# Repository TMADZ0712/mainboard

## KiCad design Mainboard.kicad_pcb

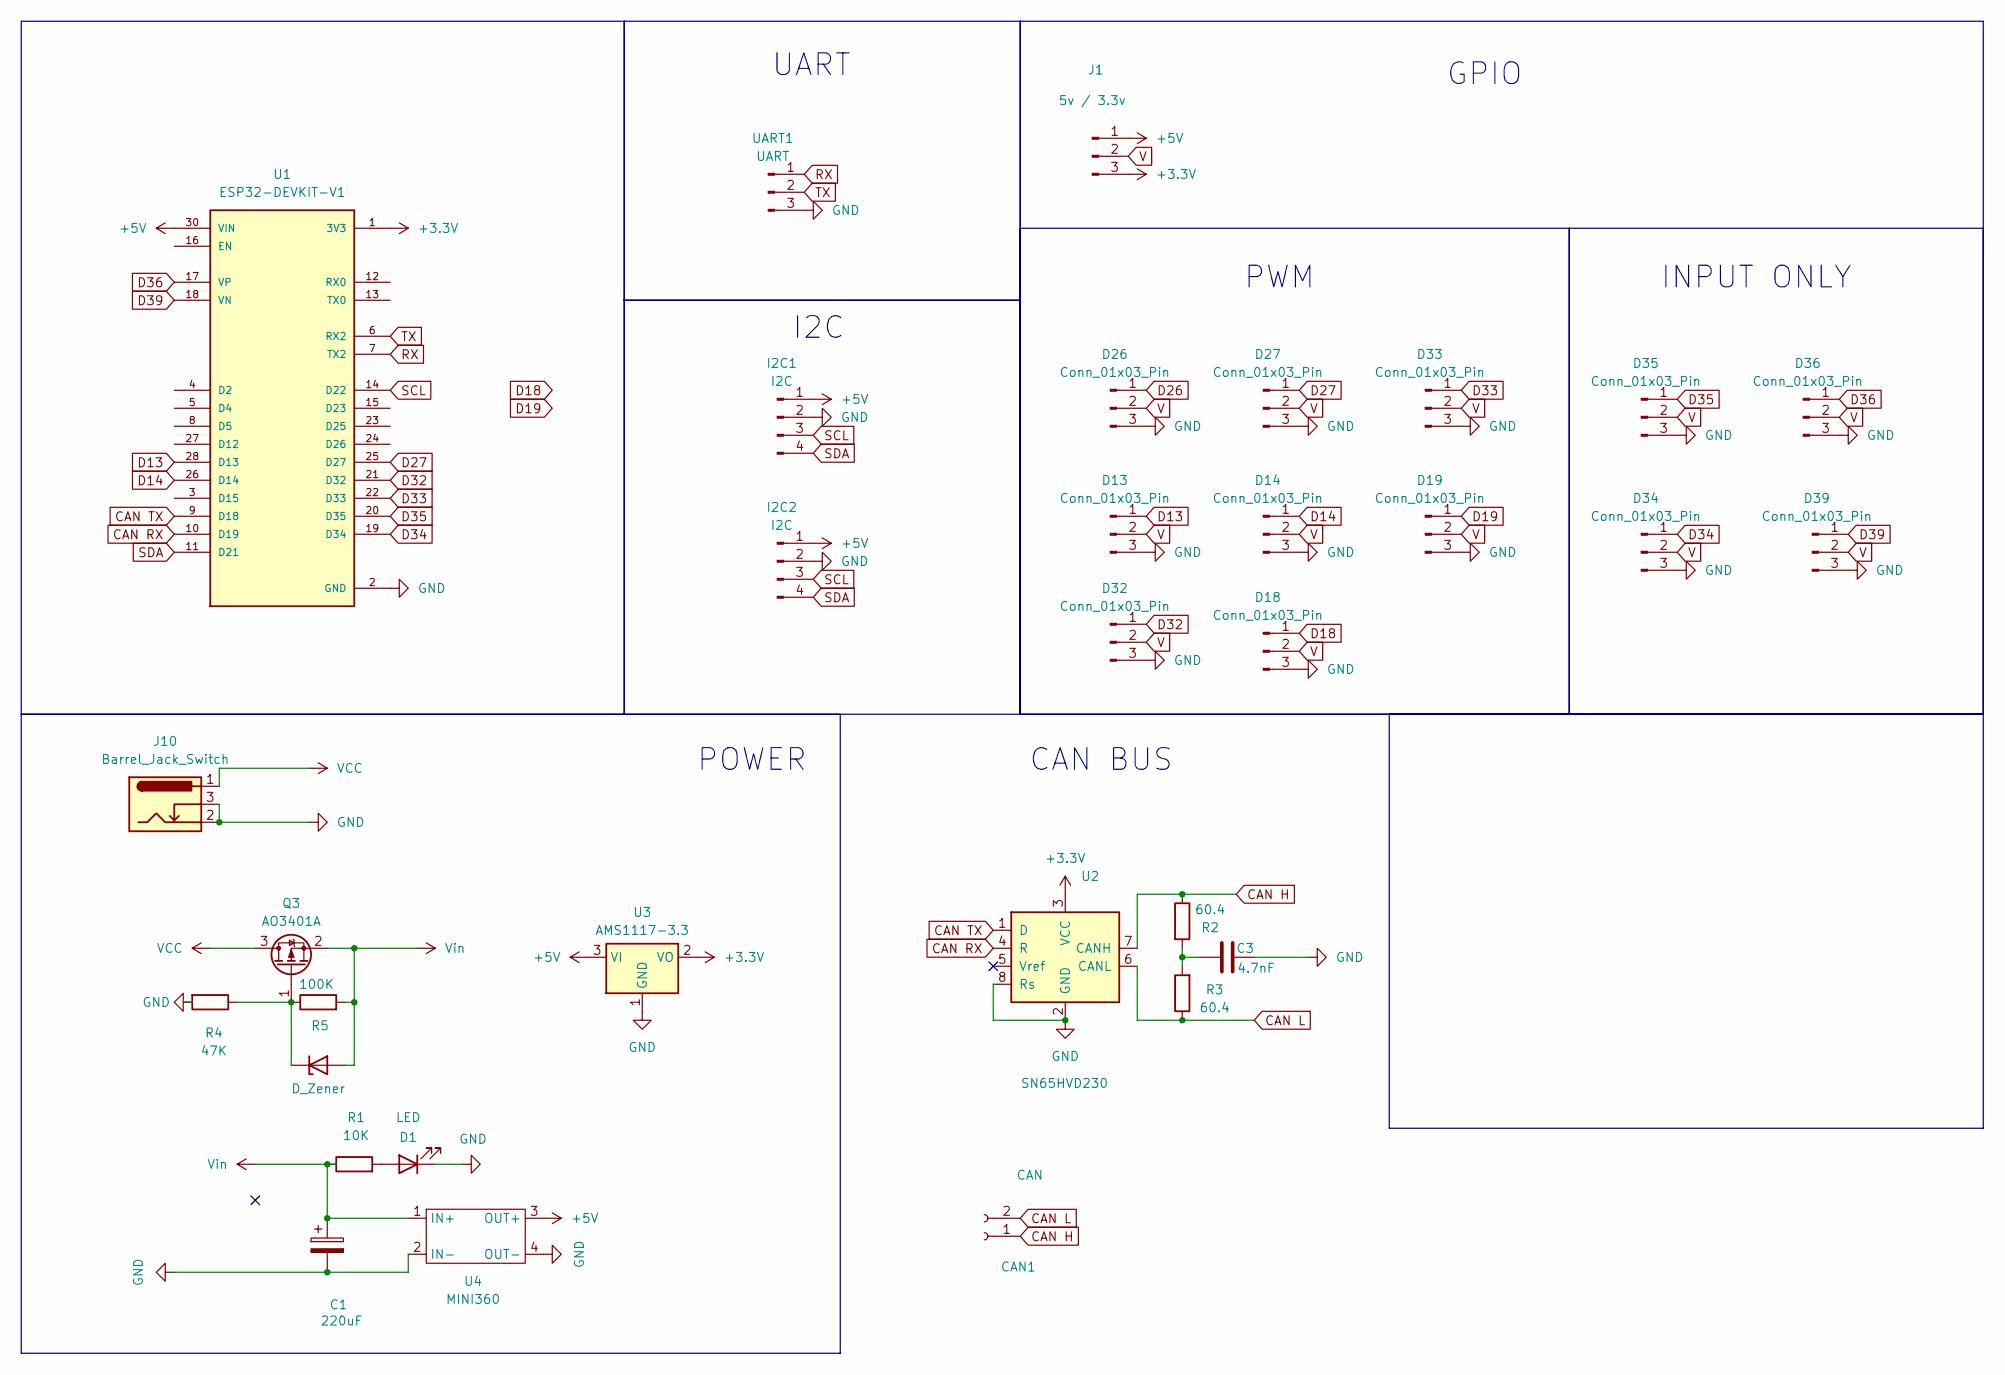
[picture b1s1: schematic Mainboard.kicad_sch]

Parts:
C1: 220uF; CP_Elec_8x10.5
C3: 4.7nF; C_0805_2012Metric_Pad1.18x1.45mm_HandSolder
CAN1: CAN; PinHeader_1x02_P2.54mm_Vertical
D1: LED; LED_1206_3216Metric_Pad1.42x1.75mm_HandSolder
D2: D_Zener; D_DO-41_SOD81_P10.16mm_Horizontal
D13, D14, D18, D19, D26, D27, D32, D33, D34, D35, D36, D39: Conn_01x03_Pin; PinHeader_1x03_P2.54mm_Vertical
I2C1, I2C2: I2C; PinHeader_1x04_P2.54mm_Vertical
J1: 5v / 3.3v; PinHeader_1x03_P2.54mm_Vertical
J10: Barrel_Jack_Switch; BarrelJack_Horizontal
Q3: AO3401A; SOT-23
R1: 10K; R_0805_2012Metric_Pad1.20x1.40mm_HandSolder
R2, R3: 60.4; R_0805_2012Metric_Pad1.20x1.40mm_HandSolder
R4: 47K; R_0805_2012Metric_Pad1.20x1.40mm_HandSolder
R5: 100K; R_0805_2012Metric_Pad1.20x1.40mm_HandSolder
U1: ESP32-DEVKIT-V1; MODULE_ESP32_DEVKIT_V1; PARTREV N/A
U2: SN65HVD230; SOIC-8_3.9x4.9mm_P1.27mm
U3: AMS1117-3.3; SOT-223-3_TabPin2
U4: MINI360; Mini360
UART1: UART; PinHeader_1x03_P2.54mm_Vertical

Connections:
+3.3V: J1.3, U1.1 (3V3), U2.3 (VCC), U3.2 (VO)
+5V: I2C1.1, I2C2.1, J1.1, U1.30 (VIN), U3.3 (VI), U4.3 (OUT+)
CAN H: CAN1.1, R2.1, U2.7 (CANH)
CAN L: CAN1.2, R3.1, U2.6 (CANL)
CAN RX: U1.10 (D19), U2.4 (R)
CAN TX: U1.9 (D18), U2.1 (D)
D13: D13.1, U1.28 (D13)
D14: D14.1, U1.26 (D14)
D26: D26.1
D27: D27.1, U1.25 (D27)
D32: D32.1, U1.21 (D32)
D33: D33.1, U1.22 (D33)
D34: D34.1, U1.19 (D34)
D35: D35.1, U1.20 (D35)
D36: D36.1, U1.17 (VP)
D39: D39.1, U1.18 (VN)
GND: C1.2, C3.2, D1.1 (K), D13.3, D14.3, D18.3, D19.3, D26.3, D27.3, D32.3, D33.3, D34.3, D35.3, D36.3, D39.3, I2C1.2, I2C2.2, J10.2, J10.3, R4.2, U1.2 (GND), U1.29 (GND), U2.2 (GND), U2.8 (Rs), U3.1 (GND), U4.2 (IN-), U4.4 (OUT-), UART1.3
unnamed: C3.1, R2.2, R3.2
unnamed: D1.2 (A), R1.2
unnamed: D2.1 (K), Q3.1 (G), R4.1, R5.1
RX: U1.7 (TX2), UART1.1
SCL: I2C1.3, I2C2.3, U1.14 (D22)
SDA: I2C1.4, I2C2.4, U1.11 (D21)
TX: U1.6 (RX2), UART1.2
V: D13.2, D14.2, D18.2, D19.2, D26.2, D27.2, D32.2, D33.2, D34.2, D35.2, D36.2, D39.2, J1.2
VCC: J10.1, Q3.3 (D)
Vin: C1.1, D2.2 (A), Q3.2 (S), R1.1, R5.2, U4.1 (IN+)

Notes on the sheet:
CAN BUS
GPIO
UART
I2C
PWM
POWER
INPUT ONLY

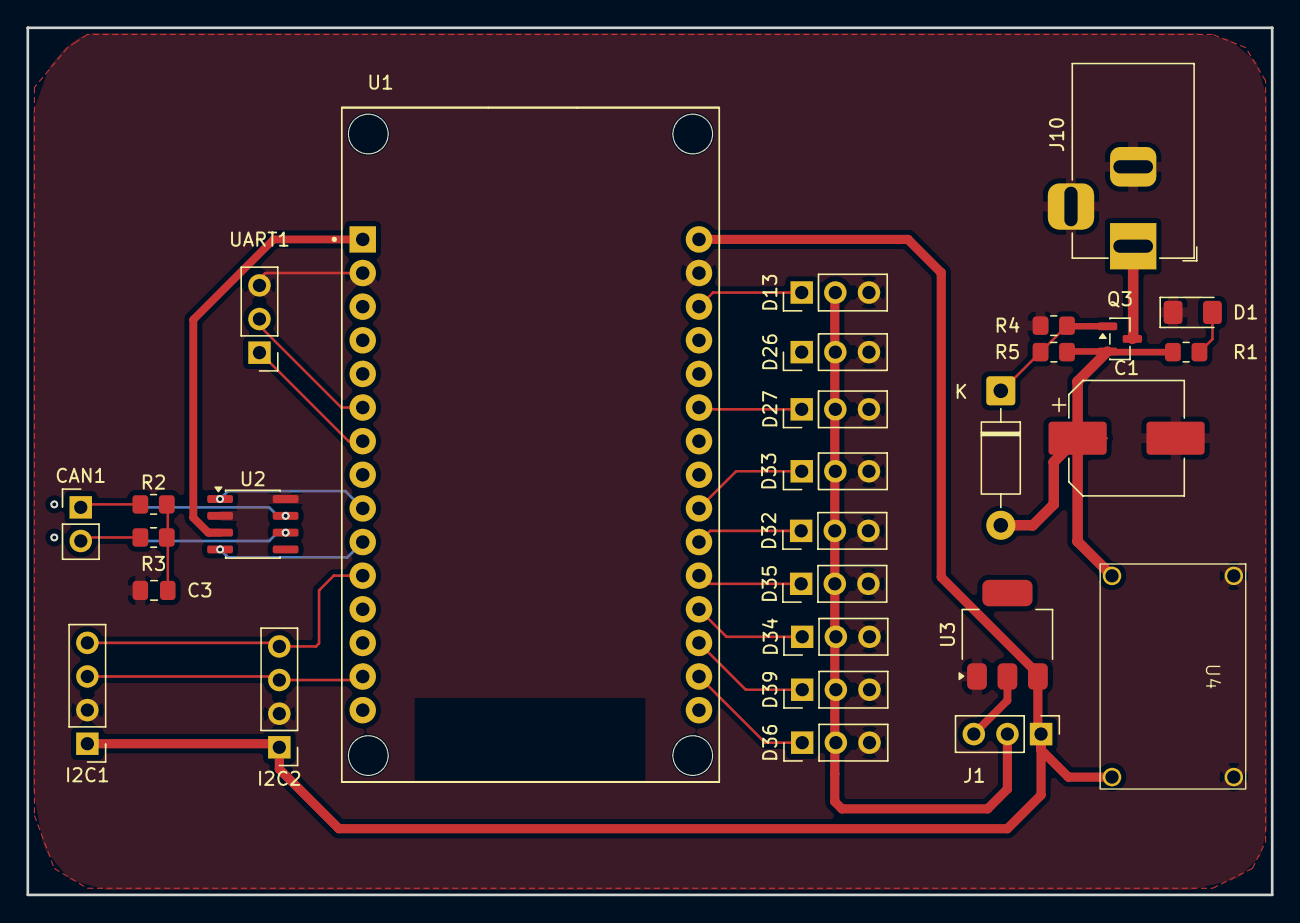
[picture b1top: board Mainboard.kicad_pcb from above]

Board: 2 copper layers, 94.0 x 65.5 mm, 29 parts (0 on the bottom side), 25 nets.
